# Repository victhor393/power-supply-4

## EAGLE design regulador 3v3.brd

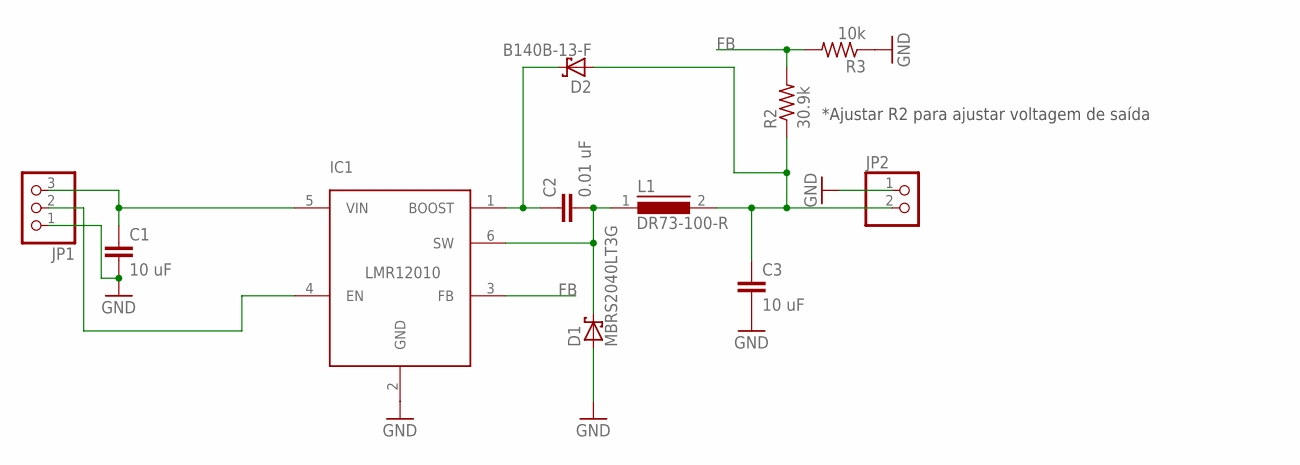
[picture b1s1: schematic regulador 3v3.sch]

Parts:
C1, C3: 10 uF; C1210
C2: 0.01 uF; C0805
D1: MBRS2040LT3G; SMB
D2: B140B-13-F; SMB
IC1: LMR12010; SOT23-6L
JP1: PINHD-1X3; 1X03
JP2: PINHD-1X2; 1X02
L1: DR73-100-R; DR73
R2: 30.9k; R0805
R3: 10k; R0805

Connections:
FB: IC1.3 (FB), R2.2, R3.2
GND: C1.2, C3.2, D1.A, IC1.2 (GND), JP1.1, JP2.1, R3.1
unnamed: IC1.4 (EN), JP1.2
unnamed: C2.1, D2.C, IC1.1 (BOOST)
unnamed: C2.2, D1.C, IC1.6 (SW), L1.1
unnamed: C3.1, D2.A, JP2.2, L1.2, R2.1
VIN: C1.1, IC1.5 (VIN), JP1.3

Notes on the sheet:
*Ajustar R2 para ajustar voltagem de saída

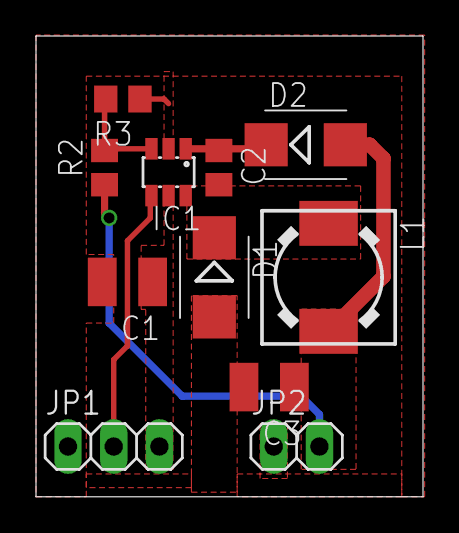
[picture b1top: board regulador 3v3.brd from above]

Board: 2 copper layers, 21.5 x 25.6 mm, 11 parts (0 on the bottom side), 7 nets.

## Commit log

2019-05-21 Added schematic and board layout in pdf format
